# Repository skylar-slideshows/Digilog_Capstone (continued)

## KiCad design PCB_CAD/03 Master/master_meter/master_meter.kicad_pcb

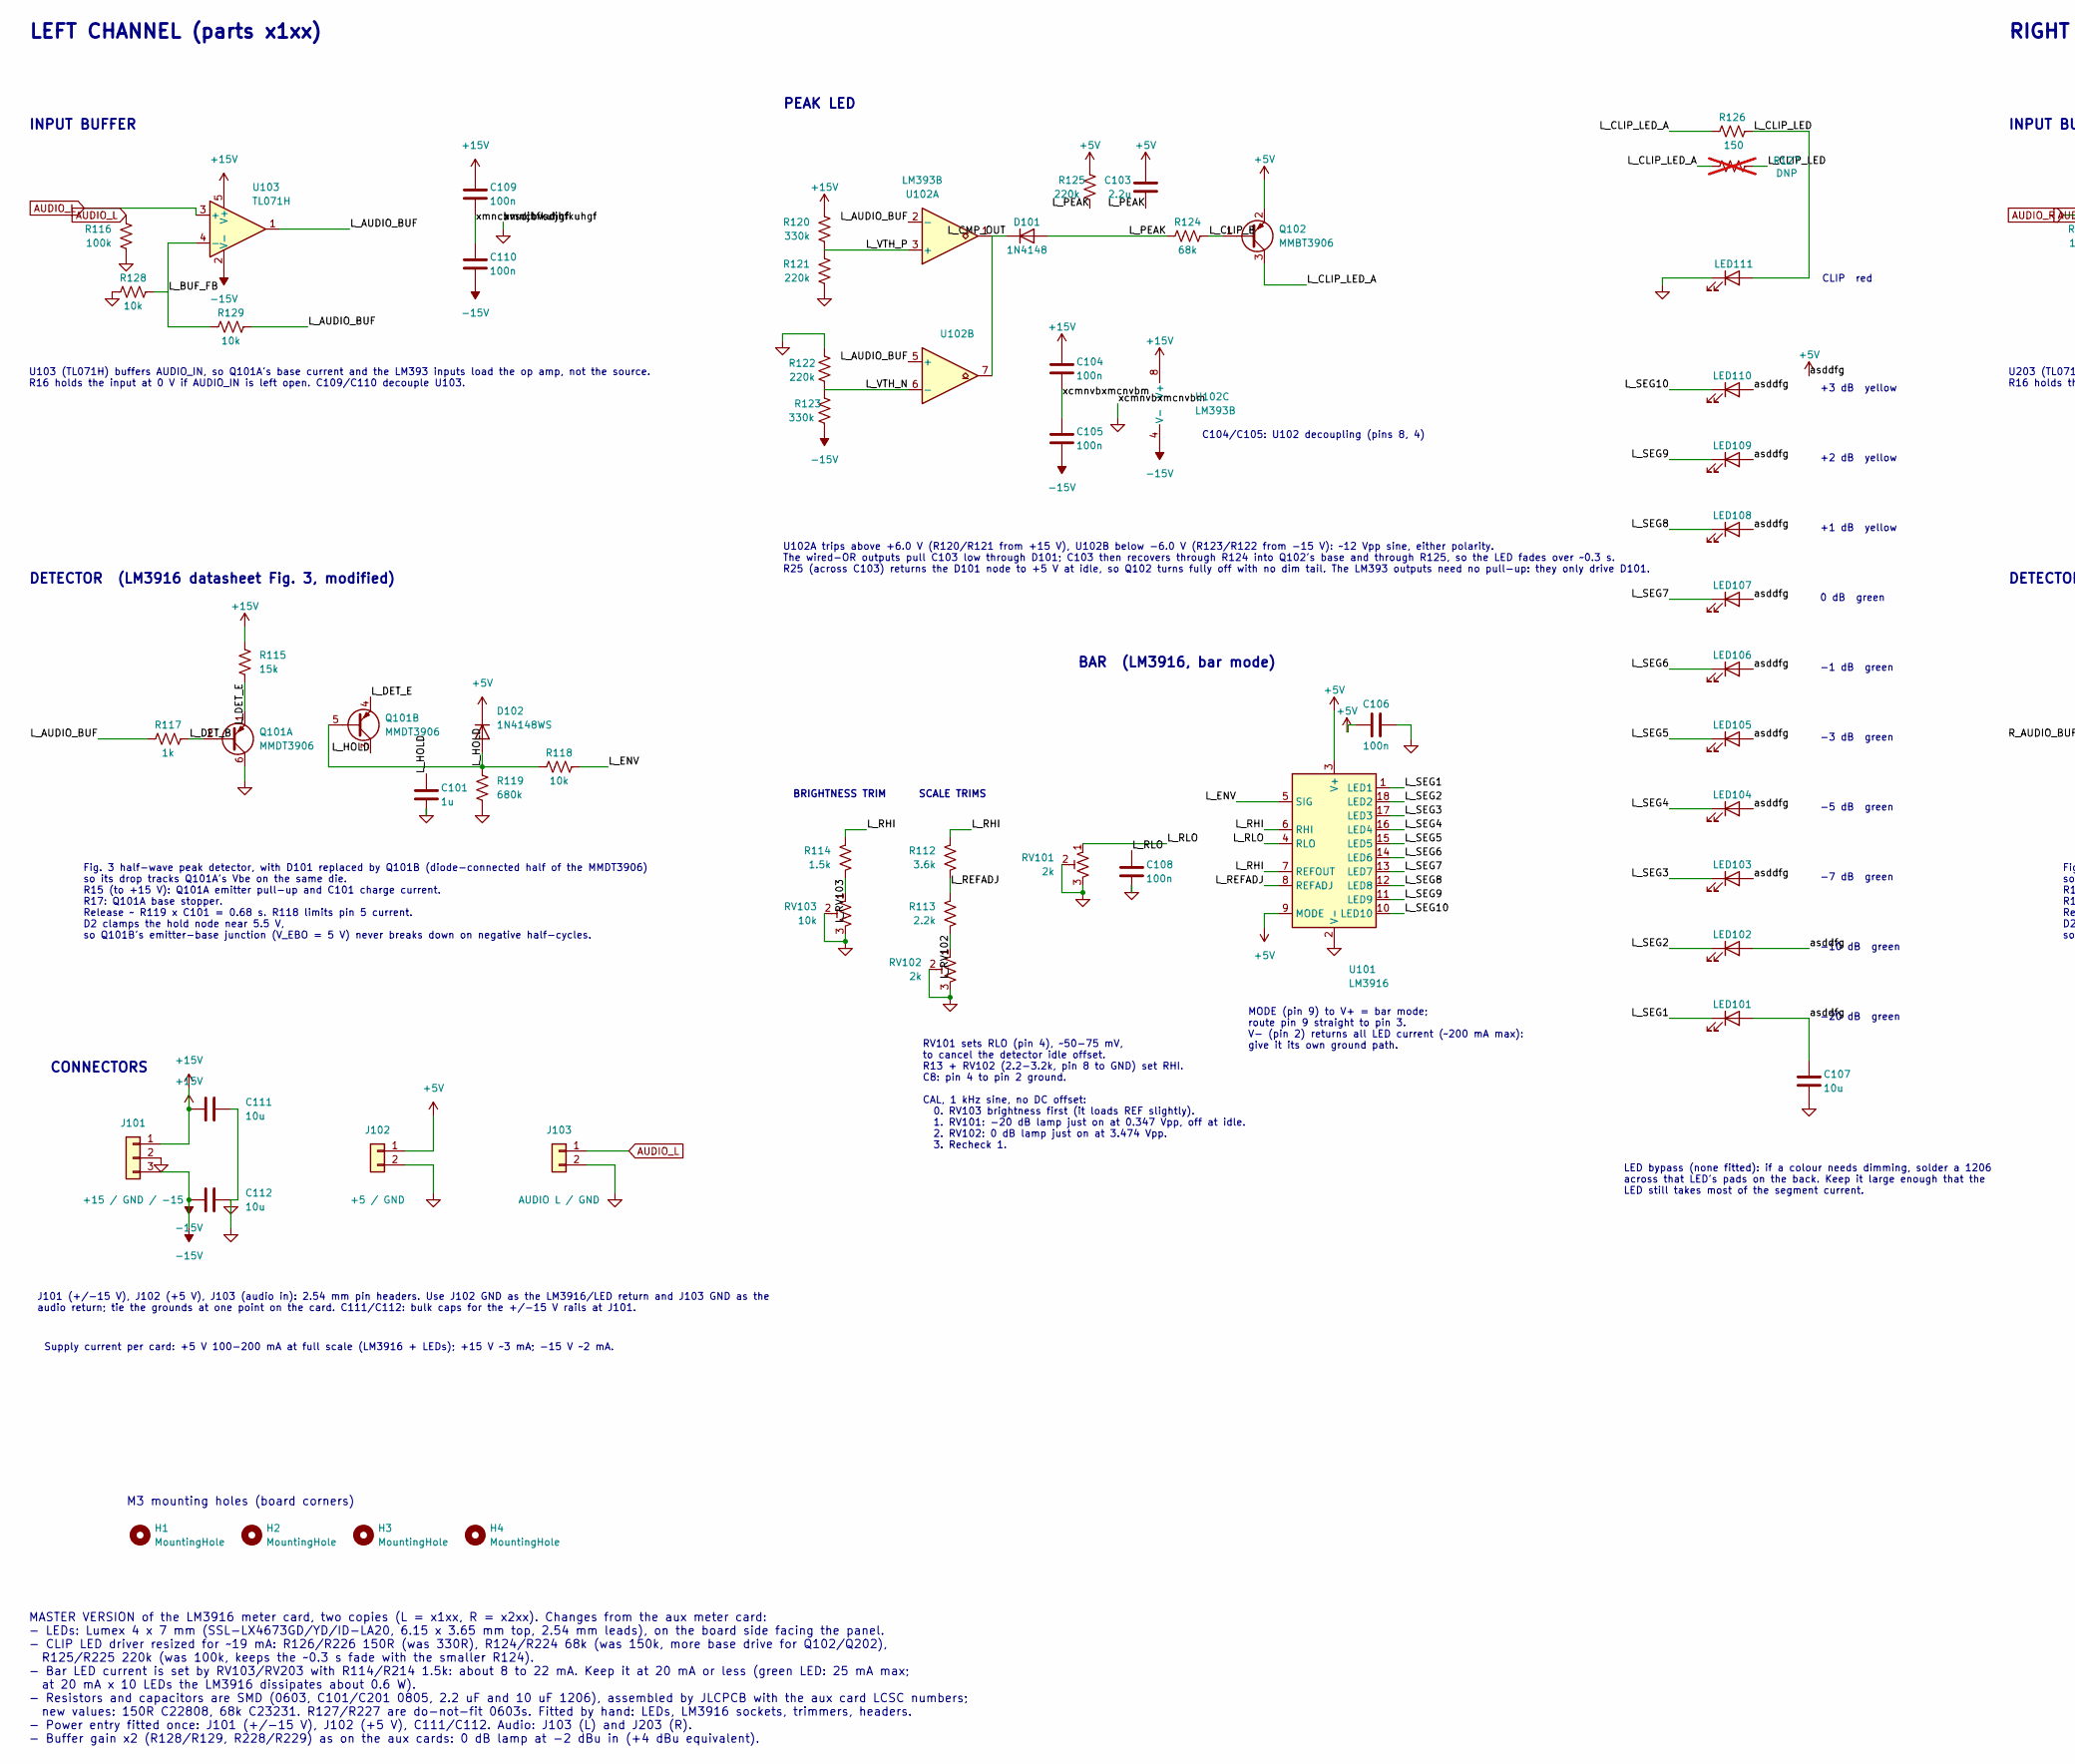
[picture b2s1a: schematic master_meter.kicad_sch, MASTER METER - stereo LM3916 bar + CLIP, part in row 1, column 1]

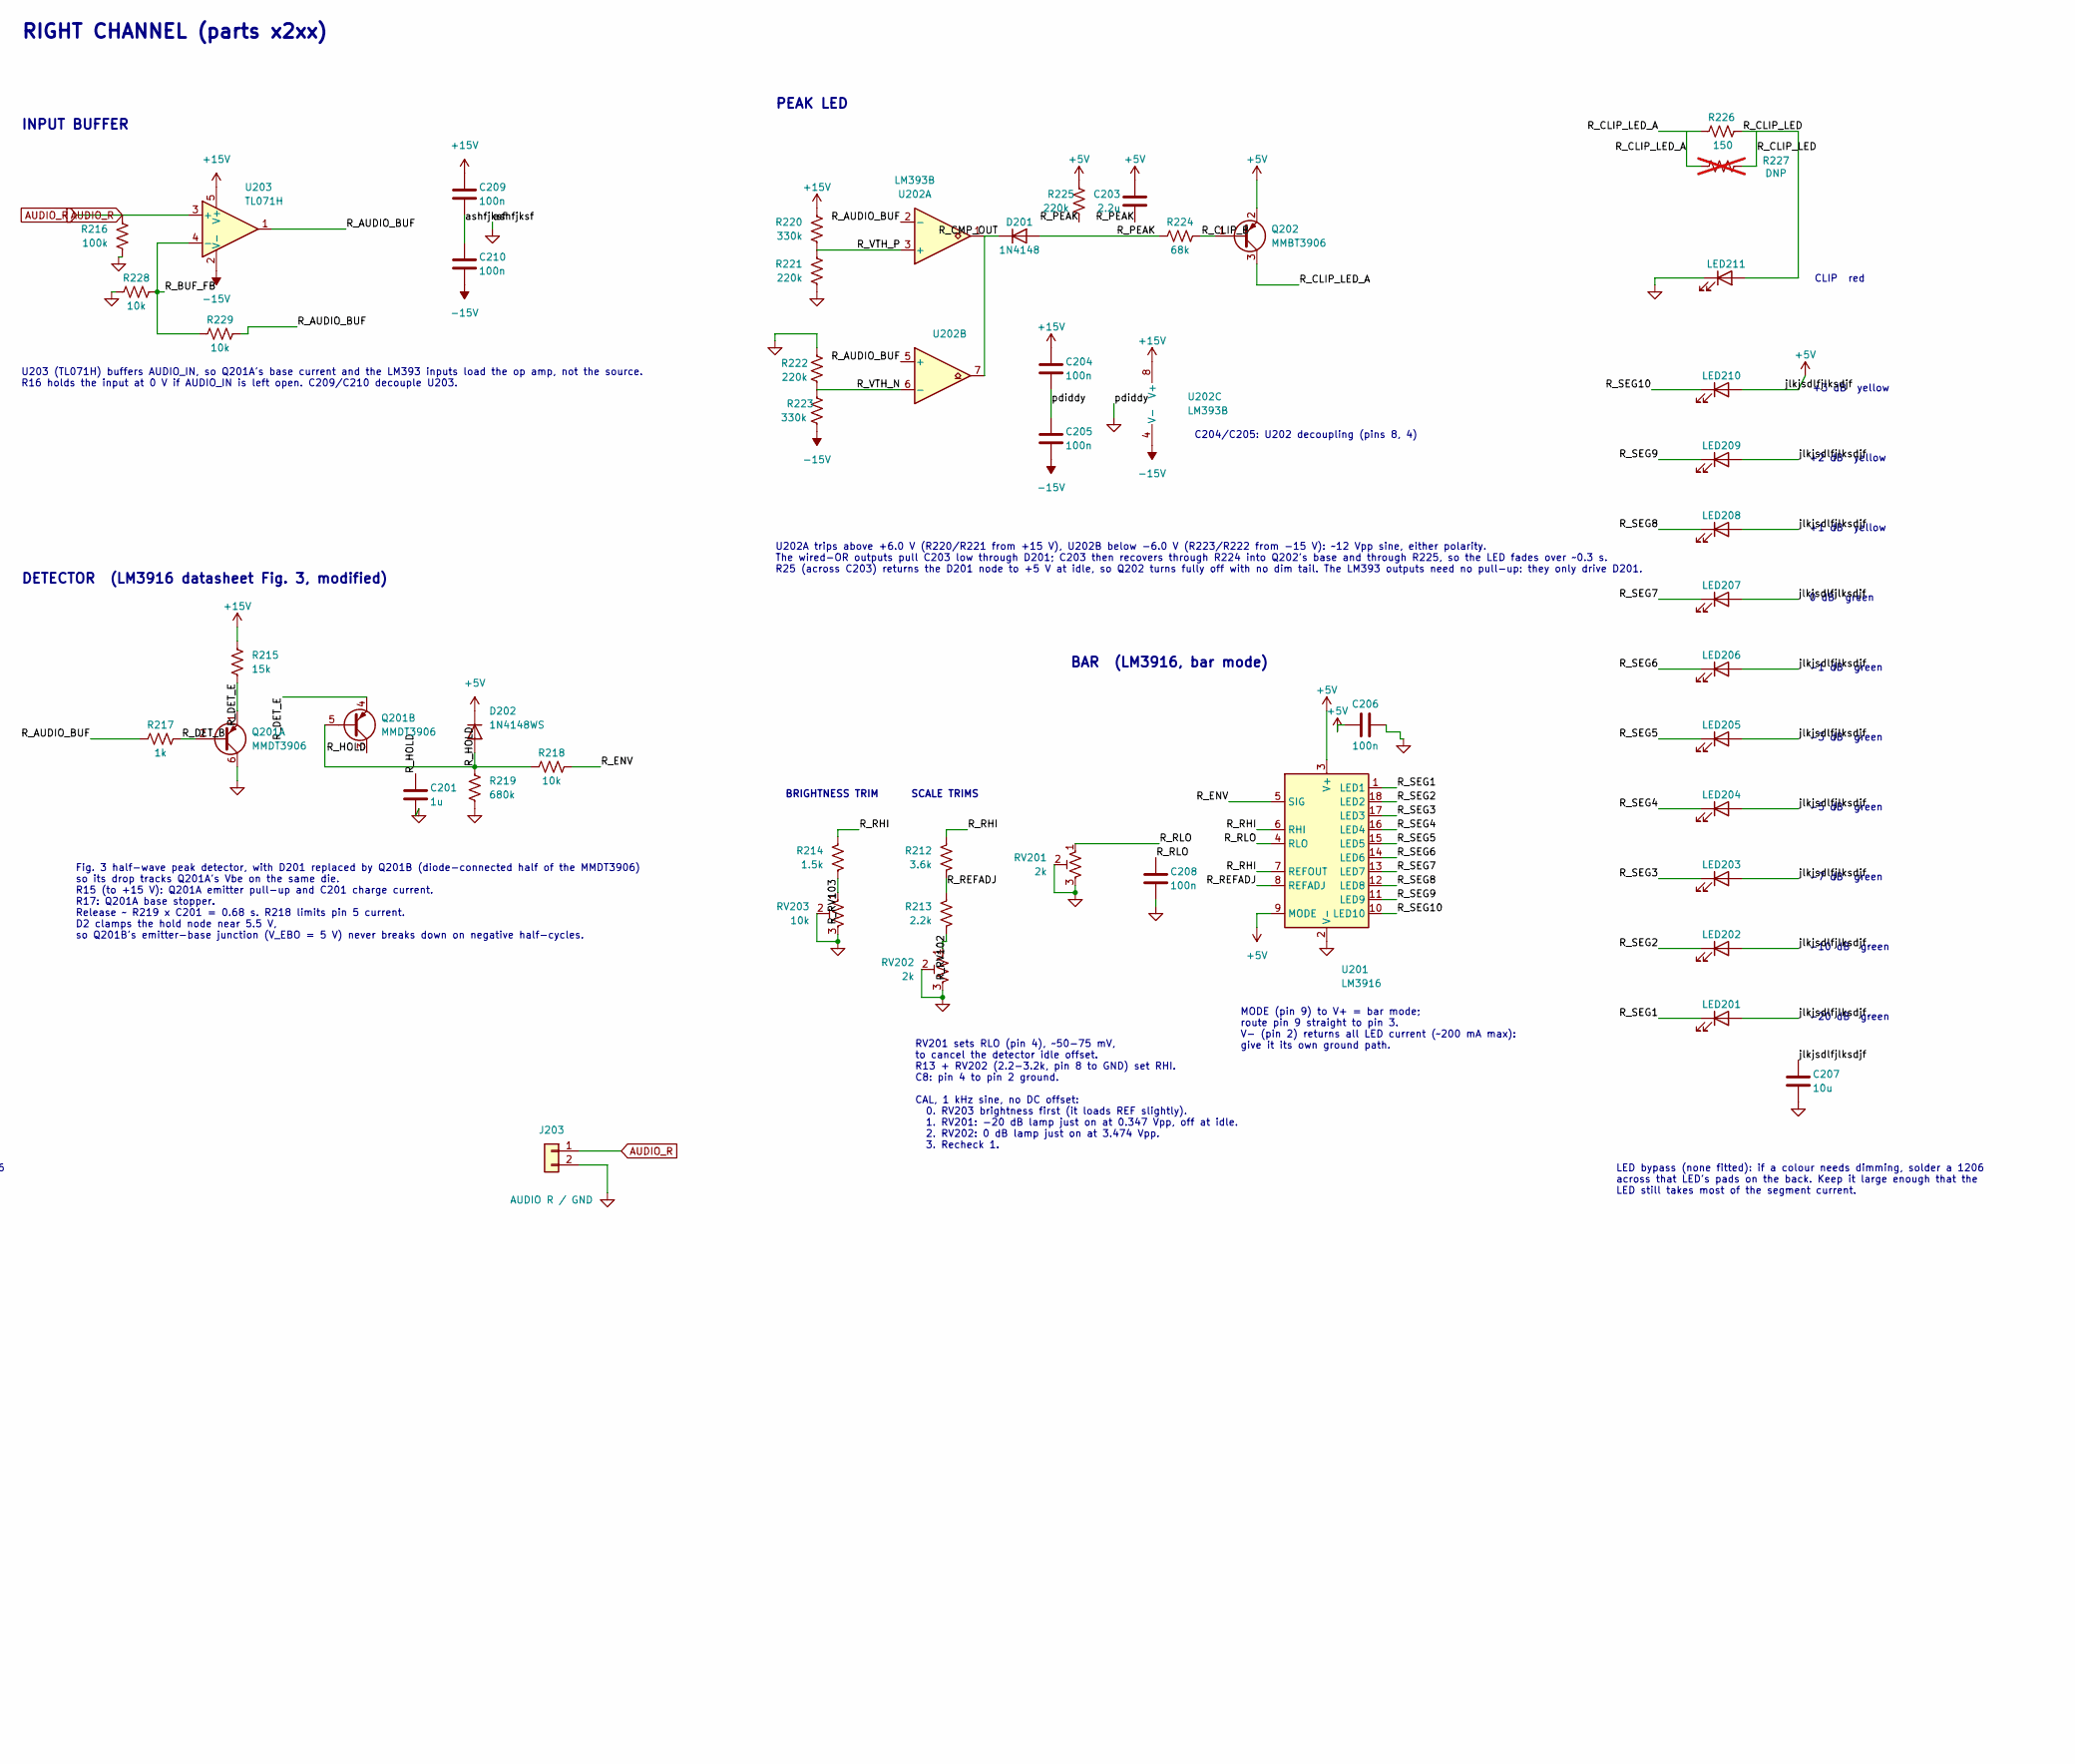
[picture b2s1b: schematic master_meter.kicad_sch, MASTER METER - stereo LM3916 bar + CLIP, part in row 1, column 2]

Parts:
C101, C201: 1u; C_0805_2012Metric; MPN Samsung CL21B105KBFNNNE; LCSC C28323
C103, C203: 2.2u; C_1206_3216Metric; MPN Samsung CL31B225KBHNNNE; LCSC C50254
C104, C105, C106, C108, C109, C110, C204, C205, C206, C208, C209, C210: 100n; C_0603_1608Metric; LCSC C1591
C107, C111, C112, C207: 10u; C_1206_3216Metric; MPN Samsung CL31A106KBHNNNE; LCSC C13585
D101, D201: 1N4148; D_SOD-323; LCSC C2128
D102, D202: 1N4148WS; D_SOD-323; MPN JSCJ 1N4148WS; LCSC C2128
H1, H2, H3, H4: MountingHole; MountingHole_3.2mm_M3
J101: +15 / GND / -15; PinHeader_1x03_P2.54mm_Vertical; LCSC DNP
J102: +5 / GND; PinHeader_1x02_P2.54mm_Vertical; LCSC DNP
J103: AUDIO L / GND; PinHeader_1x02_P2.54mm_Vertical; LCSC DNP
J203: AUDIO R / GND; PinHeader_1x02_P2.54mm_Vertical; LCSC DNP
LED101, LED102, LED103, LED104, LED105, LED106, LED107, LED201, LED202, LED203, LED204, LED205, LED206, LED207: SSL-LX4673GD-LA20 green; LED_Lumex_SSL-LX4673_6.15x3.65mm_P2.54mm; LCSC DNP
LED108, LED109, LED110, LED208, LED209, LED210: SSL-LX4673YD-LA20 yellow; LED_Lumex_SSL-LX4673_6.15x3.65mm_P2.54mm; LCSC DNP
LED111, LED211: SSL-LX4673ID-LA20 red; LED_Lumex_SSL-LX4673_6.15x3.65mm_P2.54mm; LCSC DNP
Q101, Q201: MMDT3906; SOT-363_SC-70-6; LCSC C508227
Q102, Q202: MMBT3906; SOT-23; LCSC C82762
R112, R212: 3.6k; R_0603_1608Metric; MPN UNI-ROYAL 0603WAF3601T5E; LCSC C22980
R113, R213: 2.2k; R_0603_1608Metric; MPN UNI-ROYAL 0603WAF2201T5E; LCSC C4190
R114, R214: 1.5k; R_0603_1608Metric; MPN UNI-ROYAL 0603WAF1501T5E; LCSC C22843
R115, R215: 15k; R_0603_1608Metric; MPN UNI-ROYAL 0603WAF1502T5E; LCSC C22809
R116, R216: 100k; R_0603_1608Metric; MPN UNI-ROYAL 0603WAF1003T5E; LCSC C25803
R117, R217: 1k; R_0603_1608Metric; MPN UNI-ROYAL 0603WAF1001T5E; LCSC C21190
R118, R128, R129, R218, R228, R229: 10k; R_0603_1608Metric; MPN UNI-ROYAL 0603WAF1002T5E; LCSC C25804
R119, R219: 680k; R_0603_1608Metric; MPN UNI-ROYAL 0603WAF6803T5E; LCSC C25822
R120, R123, R220, R223: 330k; R_0603_1608Metric; MPN UNI-ROYAL 0603WAF3303T5E; LCSC C23137
R121, R122, R125, R221, R222, R225: 220k; R_0603_1608Metric; MPN UNI-ROYAL 0603WAF2203T5E; LCSC C22961
R124, R224: 68k; R_0603_1608Metric; MPN UNI-ROYAL 0603WAF6802T5E; LCSC C23231
R126, R226: 150; R_0603_1608Metric; MPN UNI-ROYAL 0603WAF1500T5E; LCSC C22808
R127, R227: DNP; R_0603_1608Metric; LCSC DNP; not fitted
RV101, RV102, RV201, RV202: 2k; Potentiometer_Bourns_3006P_Horizontal; LCSC DNP
RV103, RV203: 10k; Potentiometer_Bourns_3006P_Horizontal; LCSC DNP
U101, U201: LM3916; DIP-18_W7.62mm_Socket; LCSC DNP
U102, U202: LM393B; SOIC-8_3.9x4.9mm_P1.27mm; LCSC C2865059
U103, U203: TL071H; SOT-23-5; MPN TI TL071HIDBVR; LCSC C4370629

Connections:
+5V: C103.1, C106.1, C107.1, C203.1, C206.1, C207.1, D102.1 (K), D202.1 (K), J102.1, LED101.2 (A), LED102.2 (A), LED103.2 (A), LED104.2 (A), LED105.2 (A), LED106.2 (A), LED107.2 (A), LED108.2 (A), LED109.2 (A), LED110.2 (A), LED201.2 (A), LED202.2 (A), LED203.2 (A), LED204.2 (A), LED205.2 (A), LED206.2 (A), LED207.2 (A), LED208.2 (A), LED209.2 (A), LED210.2 (A), Q102.2 (E), Q202.2 (E), R125.1, R225.1, U101.3 (V+), U101.9 (MODE), U201.3 (V+), U201.9 (MODE)
+15V: C104.1, C109.1, C111.1, C204.1, C209.1, J101.1, R115.1, R120.1, R215.1, R220.1, U102.8 (V+), U103.5 (V+), U202.8 (V+), U203.5 (V+)
-15V: C105.2, C110.2, C112.1, C205.2, C210.2, J101.3, R123.2, R223.2, U102.4 (V-), U103.2 (V-), U202.4 (V-), U203.2 (V-)
/L_AUDIO_BUF: R117.1, R129.2, U102.2 (-), U102.5 (+), U103.1
/L_BUF_FB: R128.2, R129.1, U103.4 (-)
/L_CLIP_B: Q102.1 (B), R124.2
/L_CLIP_LED: LED111.2 (A), R126.2, R127.2
/L_CLIP_LED_A: Q102.3 (C), R126.1, R127.1
/L_CMP_OUT: D101.1 (K), U102.1, U102.7
/L_DET_B: Q101.2 (B1), R117.2
/L_DET_E: Q101.1 (E1), Q101.4 (E2), R115.2
/L_ENV: R118.2, U101.5 (SIG)
/L_HOLD: C101.1, D102.2 (A), Q101.3 (C2), Q101.5 (B2), R118.1, R119.1
/L_PEAK: C103.2, D101.2 (A), R124.1, R125.2
/L_REFADJ: R112.2, R113.1, U101.8 (REFADJ)
/L_RHI: R112.1, R114.1, U101.6 (RHI), U101.7 (REFOUT)
/L_RLO: C108.1, RV101.1, U101.4 (RLO)
/L_RV102: R113.2, RV102.1
/L_RV103: R114.2, RV103.1
/L_SEG1: LED101.1 (K), U101.1 (LED1)
/L_SEG2: LED102.1 (K), U101.18 (LED2)
/L_SEG3: LED103.1 (K), U101.17 (LED3)
/L_SEG4: LED104.1 (K), U101.16 (LED4)
/L_SEG5: LED105.1 (K), U101.15 (LED5)
/L_SEG6: LED106.1 (K), U101.14 (LED6)
/L_SEG7: LED107.1 (K), U101.13 (LED7)
/L_SEG8: LED108.1 (K), U101.12 (LED8)
/L_SEG9: LED109.1 (K), U101.11 (LED9)
/L_SEG10: LED110.1 (K), U101.10 (LED10)
/L_VTH_N: R122.2, R123.1, U102.6 (-)
/L_VTH_P: R120.2, R121.1, U102.3 (+)
/R_AUDIO_BUF: R217.1, R229.2, U202.2 (-), U202.5 (+), U203.1
/R_BUF_FB: R228.2, R229.1, U203.4 (-)
/R_CLIP_B: Q202.1 (B), R224.2
/R_CLIP_LED: LED211.2 (A), R226.2, R227.2
/R_CLIP_LED_A: Q202.3 (C), R226.1, R227.1
/R_CMP_OUT: D201.1 (K), U202.1, U202.7
/R_DET_B: Q201.2 (B1), R217.2
/R_DET_E: Q201.1 (E1), Q201.4 (E2), R215.2
/R_ENV: R218.2, U201.5 (SIG)
/R_HOLD: C201.1, D202.2 (A), Q201.3 (C2), Q201.5 (B2), R218.1, R219.1
/R_PEAK: C203.2, D201.2 (A), R224.1, R225.2
/R_REFADJ: R212.2, R213.1, U201.8 (REFADJ)
/R_RHI: R212.1, R214.1, U201.6 (RHI), U201.7 (REFOUT)
/R_RLO: C208.1, RV201.1, U201.4 (RLO)
/R_RV102: R213.2, RV202.1
/R_RV103: R214.2, RV203.1
/R_SEG1: LED201.1 (K), U201.1 (LED1)
/R_SEG2: LED202.1 (K), U201.18 (LED2)
/R_SEG3: LED203.1 (K), U201.17 (LED3)
/R_SEG4: LED204.1 (K), U201.16 (LED4)
/R_SEG5: LED205.1 (K), U201.15 (LED5)
/R_SEG6: LED206.1 (K), U201.14 (LED6)
/R_SEG7: LED207.1 (K), U201.13 (LED7)
/R_SEG8: LED208.1 (K), U201.12 (LED8)
/R_SEG9: LED209.1 (K), U201.11 (LED9)
/R_SEG10: LED210.1 (K), U201.10 (LED10)
/R_VTH_N: R222.2, R223.1, U202.6 (-)
/R_VTH_P: R220.2, R221.1, U202.3 (+)
AUDIO_L: J103.1, R116.1, U103.3 (+)
AUDIO_R: J203.1, R216.1, U203.3 (+)
GND: C101.2, C104.2, C105.1, C106.2, C107.2, C108.2, C109.2, C110.1, C111.2, C112.2, C201.2, C204.2, C205.1, C206.2, C207.2, C208.2, C209.2, C210.1, J101.2, J102.2, J103.2, J203.2, LED111.1 (K), LED211.1 (K), Q101.6 (C1), Q201.6 (C1), R116.2, R119.2, R121.2, R122.1, R128.1, R216.2, R219.2, R221.2, R222.1, R228.1, RV101.2, RV101.3, RV102.2, RV102.3, RV103.2, RV103.3, RV201.2, RV201.3, RV202.2, RV202.3, RV203.2, RV203.3, U101.2 (V-), U201.2 (V-)

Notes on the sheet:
CLIP red
-20 dB green
U103 (TL071H) buffers AUDIO_IN, so Q101A's base current and the LM393 inputs load the op amp, not the source. R16 holds the input at 0 V if AUDIO_IN is left open. C109/C110 decouple U103.
LED bypass (none fitted): if a colour needs dimming, solder a 1206 across that LED's pads on the back. Keep it large enough that the LED still takes most of the segment current.
-3 dB green
DETECTOR (LM3916 datasheet Fig. 3, modified)
U202A trips above +6.0 V (R220/R221 from +15 V), U202B below -6.0 V (R223/R222 from -15 V): ~12 Vpp sine, either polarity. The wired-OR outputs pull C203 low through D201; C203 then recovers through R224 into Q202's base and through R225, so the LED fades over ~0.3 s. R25 (across C203) returns the 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
+1 dB yellow
+3 dB yellow
M3 mounting holes (board corners)
-10 dB green
U203 (TL071H) buffers AUDIO_IN, so Q201A's base current and the LM393 inputs load the op amp, not the source. R16 holds the input at 0 V if AUDIO_IN is left open. C209/C210 decouple U203.
BAR (LM3916, bar mode)
-5 dB green
C104/C105: U102 decoupling (pins 8, 4)
-1 dB green
+2 dB yellow
MODE (pin 9) to V+ = bar mode; route pin 9 straight to pin 3. V- (pin 2) returns all LED current (~200 mA max): give it its own ground path.
CONNECTORS
-7 dB green
INPUT BUFFER
PEAK LED
0 dB green
U102A trips above +6.0 V (R120/R121 from +15 V), U102B below -6.0 V (R123/R122 from -15 V): ~12 Vpp sine, either polarity. The wired-OR outputs pull C103 low through D101; C103 then recovers through R124 into Q102's base and through R125, so the LED fades over ~0.3 s. R25 (across C103) returns the 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
BRIGHTNESS TRIM
RIGHT CHANNEL (parts x2xx)
MASTER VERSION of the LM3916 meter card, two copies (L = x1xx, R = x2xx). Changes from the aux meter card: - LEDs: Lumex 4 x 7 mm (SSL-LX4673GD/YD/ID-LA20, 6.15 x 3.65 mm top, 2.54 mm leads), on the board side facing the panel. - CLIP LED driver resized for ~19 mA: R126/R226 150R (was 330R), R124/R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
Fig. 3 half-wave peak detector, with D201 replaced by Q201B (diode-connected half of the MMDT3906) so its drop tracks Q201A's Vbe on the same die. R15 (to +15 V): Q201A emitter pull-up and C201 charge current. R17: Q201A base stopper. Release ~ R219 x C201 = 0.68 s. R218 limits pin 5 current. D2 cl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
Supply current per card: +5 V 100-200 mA at full scale (LM3916 + LEDs); +15 V ~3 mA; -15 V ~2 mA.
RV101 sets RLO (pin 4), ~50-75 mV, to cancel the detector idle offset. R13 + RV102 (2.2-3.2k, pin 8 to GND) set RHI. C8: pin 4 to pin 2 ground. CAL, 1 kHz sine, no DC offset: 0. RV103 brightness first (it loads REF slightly). 1. RV101: -20 dB lamp just on at 0.347 Vpp, off at idle. 2. RV102: 0 dB l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
SCALE TRIMS
LEFT CHANNEL (parts x1xx)
RV201 sets RLO (pin 4), ~50-75 mV, to cancel the detector idle offset. R13 + RV202 (2.2-3.2k, pin 8 to GND) set RHI. C8: pin 4 to pin 2 ground. CAL, 1 kHz sine, no DC offset: 0. RV203 brightness first (it loads REF slightly). 1. RV201: -20 dB lamp just on at 0.347 Vpp, off at idle. 2. RV202: 0 dB l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
C204/C205: U202 decoupling (pins 8, 4)
J101 (+/-15 V), J102 (+5 V), J103 (audio in): 2.54 mm pin headers. Use J102 GND as the LM3916/LED return and J103 GND as the audio return; tie the grounds at one point on the card. C111/C112: bulk caps for the +/-15 V rails at J101.
Fig. 3 half-wave peak detector, with D101 replaced by Q101B (diode-connected half of the MMDT3906) so its drop tracks Q101A's Vbe on the same die. R15 (to +15 V): Q101A emitter pull-up and C101 charge current. R17: Q101A base stopper. Release ~ R119 x C101 = 0.68 s. R118 limits pin 5 current. D2 cl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

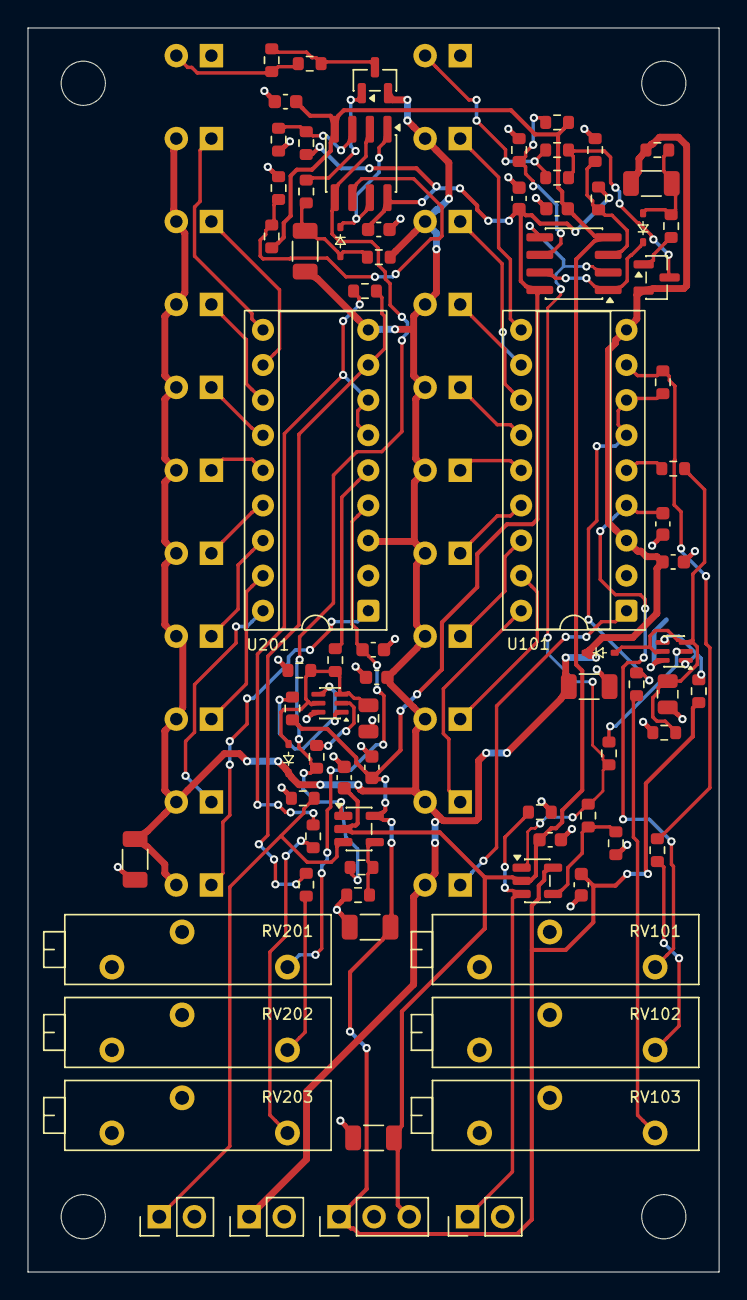
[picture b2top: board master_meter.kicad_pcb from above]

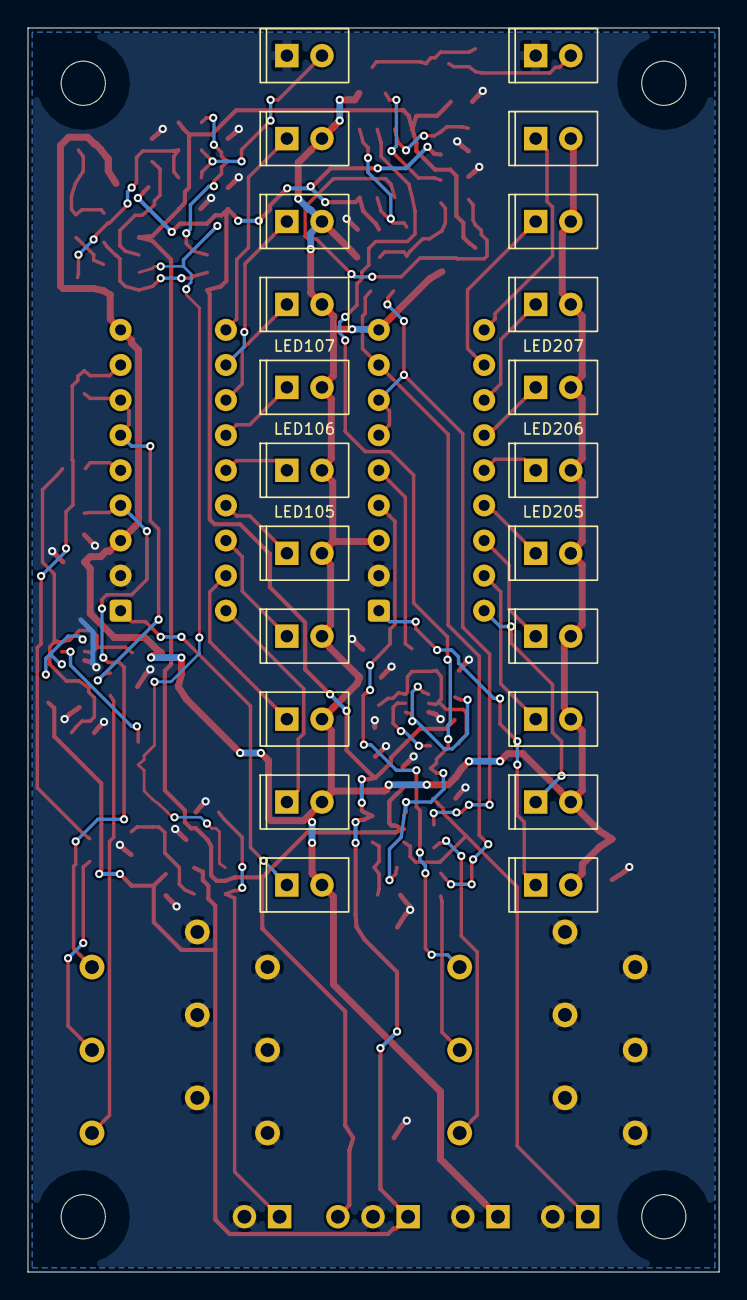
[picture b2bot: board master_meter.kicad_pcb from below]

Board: 2 copper layers, 50.0 x 90.0 mm, 106 parts (22 on the bottom side), 62 nets.

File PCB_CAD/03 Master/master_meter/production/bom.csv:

Designator,Footprint,Quantity,Value,LCSC Part #
"C101, C201",0805,2,1u,C28323
"C103, C203",1206,2,2.2u,C50254
"C104, C105, C106, C108, C109, C110, C204, C205, C206, C208, C209, C210",0603,12,100n,C1591
"C107, C111, C112, C207",1206,4,10u,C13585
"D101, D201",D_SOD-323,2,1N4148,C2128
"D102, D202",D_SOD-323,2,1N4148WS,C2128
J101,PinHeader_1x03_P2.54mm_Vertical,1,+15 / GND / -15,DNP
J102,PinHeader_1x02_P2.54mm_Vertical,1,+5 / GND,DNP
J103,PinHeader_1x02_P2.54mm_Vertical,1,AUDIO L / GND,DNP
J203,PinHeader_1x02_P2.54mm_Vertical,1,AUDIO R / GND,DNP
"LED101, LED102, LED103, LED104, LED105, LED106, LED107, LED201, LED202, LED203, LED204, LED205, LED206, LED207",LED_Lumex_SSL-LX4673_6.15x3.65mm_P2.54mm,14,SSL-LX4673GD-LA20 green,DNP
"LED108, LED109, LED110, LED208, LED209, LED210",LED_Lumex_SSL-LX4673_6.15x3.65mm_P2.54mm,6,SSL-LX4673YD-LA20 yellow,DNP
"LED111, LED211",LED_Lumex_SSL-LX4673_6.15x3.65mm_P2.54mm,2,SSL-LX4673ID-LA20 red,DNP
"Q101, Q201",SOT-363_SC-70-6,2,MMDT3906,C508227
"Q102, Q202",SOT-23,2,MMBT3906,C82762
"R112, R212",0603,2,3.6k,C22980
"R113, R213",0603,2,2.2k,C4190
"R114, R214",0603,2,1.5k,C22843
"R115, R215",0603,2,15k,C22809
"R116, R216",0603,2,100k,C25803
"R117, R217",0603,2,1k,C21190
"R118, R128, R129, R218, R228, R229",0603,6,10k,C25804
"R119, R219",0603,2,680k,C25822
"R120, R123, R220, R223",0603,4,330k,C23137
"R121, R122, R125, R221, R222, R225",0603,6,220k,C22961
"R124, R224",0603,2,68k,C23231
"R126, R226",0603,2,150,C22808
"RV101, RV102, RV201, RV202",Potentiometer_Bourns_3006P_Horizontal,4,2k,DNP
"RV103, RV203",Potentiometer_Bourns_3006P_Horizontal,2,10k,DNP
"U101, U201",DIP-18_W7.62mm_Socket,2,LM3916,DNP
"U102, U202",SOIC-8_3.9x4.9mm_P1.27mm,2,LM393B,C2865059
"U103, U203",SOT-23-5,2,TL071H,C4370629

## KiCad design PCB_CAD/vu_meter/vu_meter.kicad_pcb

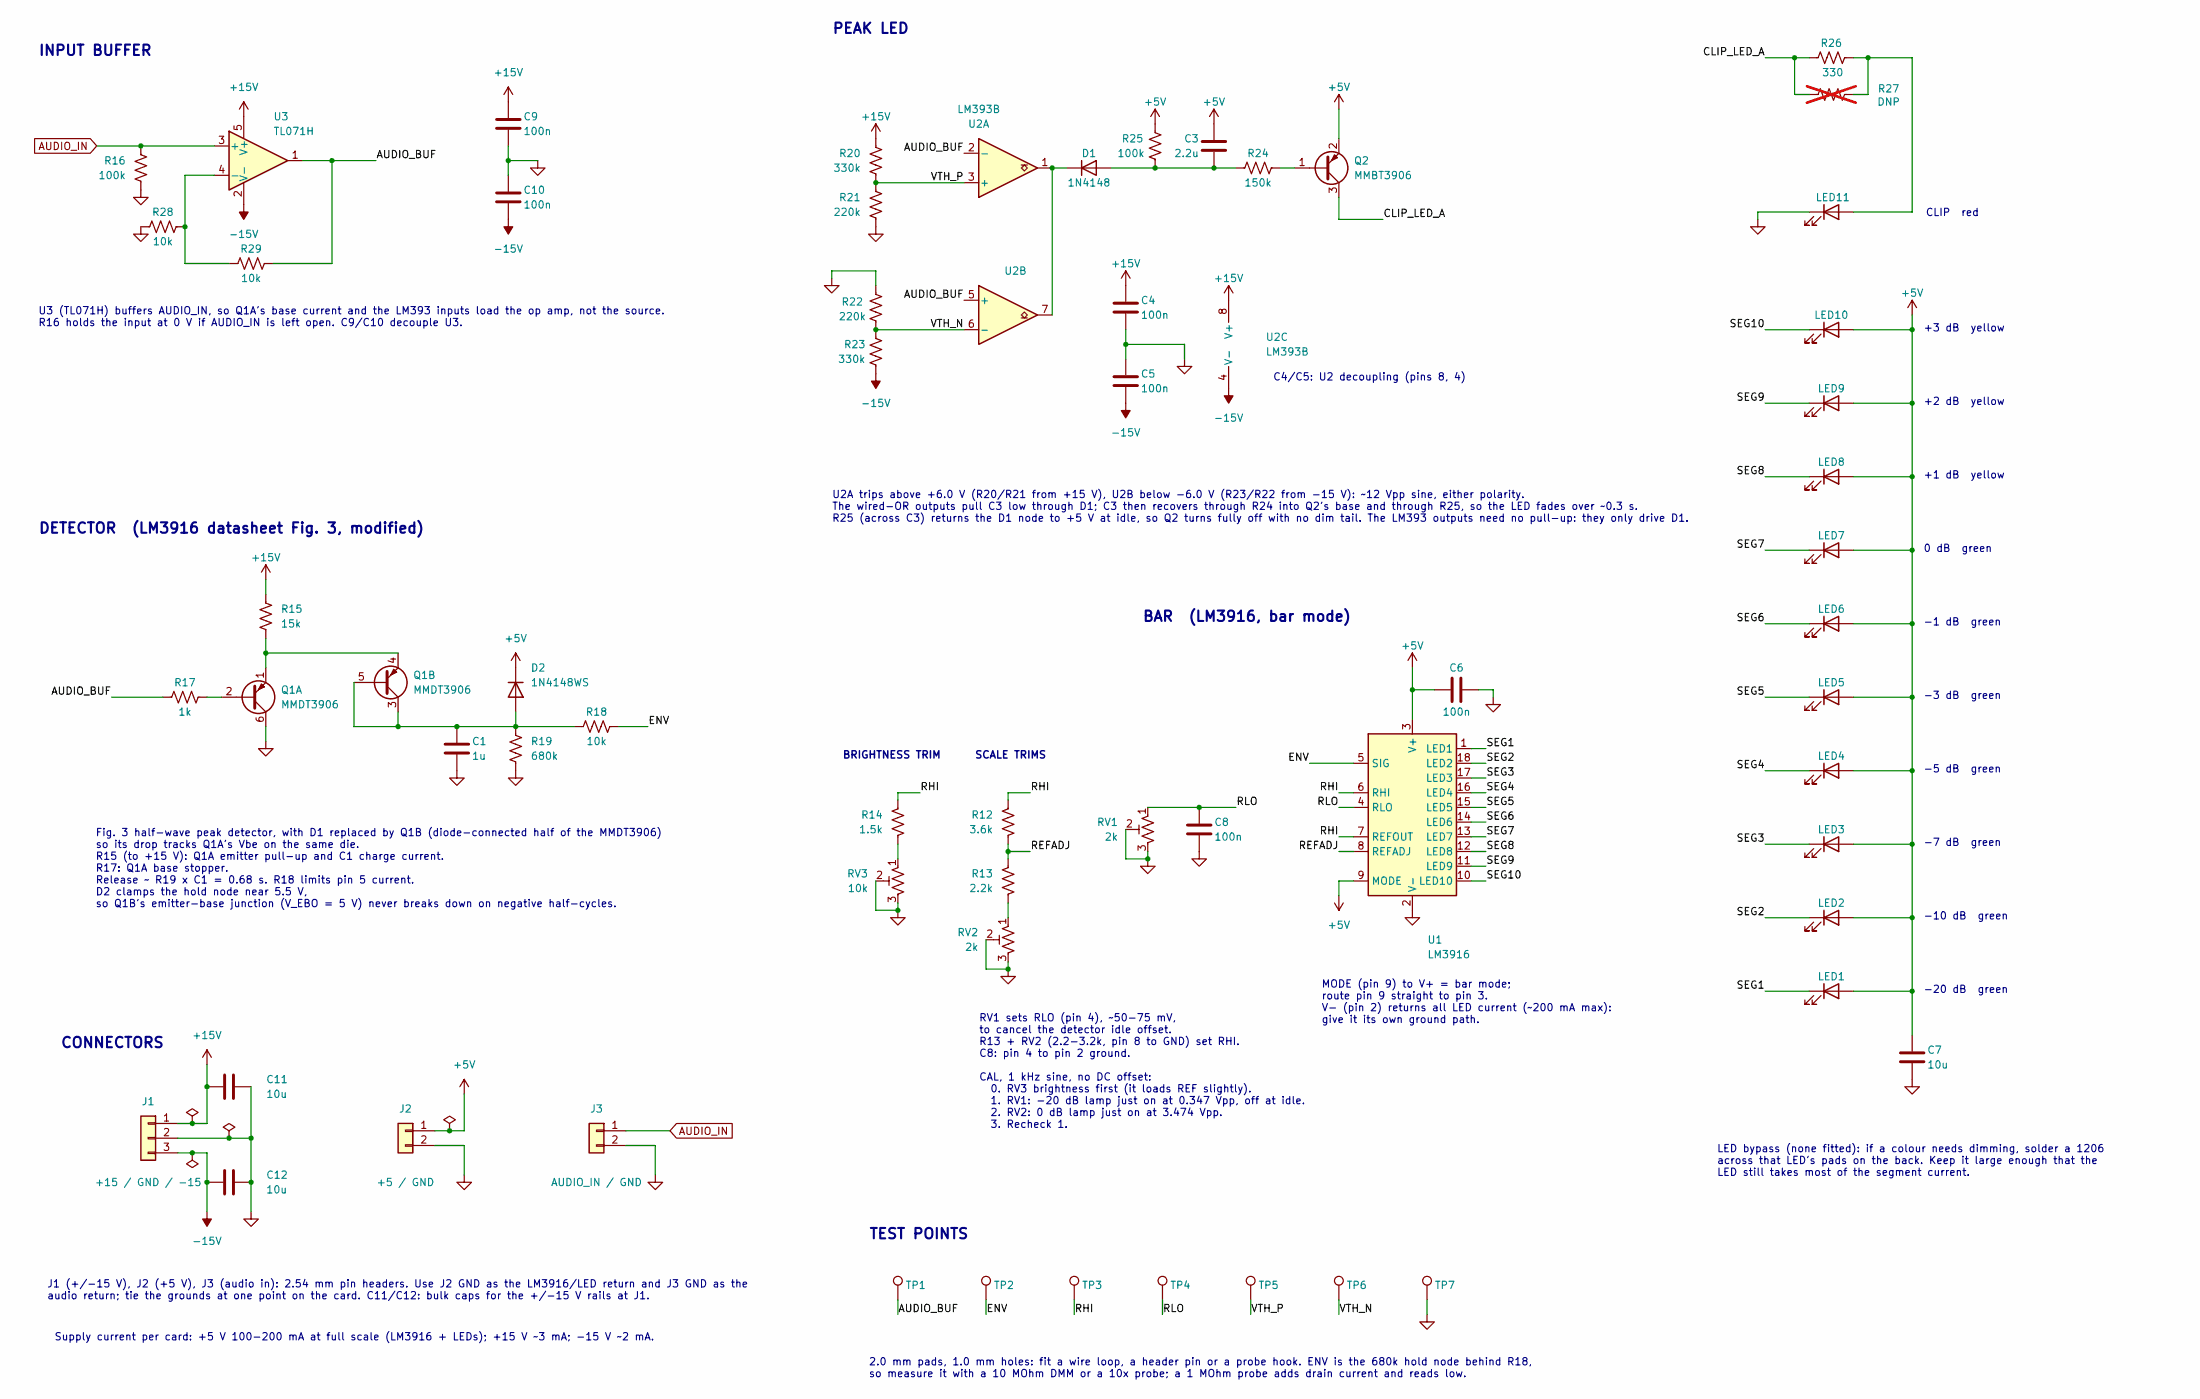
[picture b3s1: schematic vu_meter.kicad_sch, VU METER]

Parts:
C1: 1u; C_0805_2012Metric; MPN Samsung CL21B105KBFNNNE; LCSC C28323
C3: 2.2u; C_1206_3216Metric; MPN Samsung CL31B225KBHNNNE; LCSC C50254
C4, C5, C6, C8, C9, C10: 100n; C_0603_1608Metric; LCSC C1591
C7, C11, C12: 10u; C_1206_3216Metric; MPN Samsung CL31A106KBHNNNE; LCSC C13585
D1: 1N4148; D_SOD-323; LCSC C2128
D2: 1N4148WS; D_SOD-323; MPN JSCJ 1N4148WS; LCSC C2128
J1: +15 / GND / -15; PinHeader_1x03_P2.54mm_Vertical; LCSC DNP
J2: +5 / GND; PinHeader_1x02_P2.54mm_Vertical; LCSC DNP
J3: AUDIO_IN / GND; PinHeader_1x02_P2.54mm_Vertical; LCSC DNP
LED1, LED2, LED3, LED4, LED5, LED6, LED7: LED green; LED_Rectangular_W5.0mm_H2.0mm; LCSC DNP
LED8, LED9, LED10: LED yellow; LED_Rectangular_W5.0mm_H2.0mm; LCSC DNP
LED11: PEAK red; LED_Rectangular_W5.0mm_H2.0mm; LCSC DNP
Q1: MMDT3906; SOT-363_SC-70-6; LCSC C508227
Q2: MMBT3906; SOT-23; LCSC C82762
R12: 3.6k; R_0603_1608Metric; MPN UNI-ROYAL 0603WAF3601T5E; LCSC C22980
R13: 2.2k; R_0603_1608Metric; MPN UNI-ROYAL 0603WAF2201T5E; LCSC C4190
R14: 1.5k; R_0603_1608Metric; MPN UNI-ROYAL 0603WAF1501T5E; LCSC C22843
R15: 15k; R_0603_1608Metric; MPN UNI-ROYAL 0603WAF1502T5E; LCSC C22809
R16, R25: 100k; R_0603_1608Metric; MPN UNI-ROYAL 0603WAF1003T5E; LCSC C25803
R17: 1k; R_0603_1608Metric; MPN UNI-ROYAL 0603WAF1001T5E; LCSC C21190
R18, R28, R29: 10k; R_0603_1608Metric; MPN UNI-ROYAL 0603WAF1002T5E; LCSC C25804
R19: 680k; R_0603_1608Metric; MPN UNI-ROYAL 0603WAF6803T5E; LCSC C25822
R20, R23: 330k; R_0603_1608Metric; MPN UNI-ROYAL 0603WAF3303T5E; LCSC C23137
R21, R22: 220k; R_0603_1608Metric; MPN UNI-ROYAL 0603WAF2203T5E; LCSC C22961
R24: 150k; R_0603_1608Metric; MPN UNI-ROYAL 0603WAF1503T5E; LCSC C22807
R26: 330; R_0603_1608Metric; MPN UNI-ROYAL 0603WAF3300T5E; LCSC C23138
R27: DNP; R_Axial_DIN0207_L6.3mm_D2.5mm_P7.62mm_Horizontal; LCSC DNP; not fitted
RV1, RV2: 2k; Potentiometer_Bourns_3006P_Horizontal; LCSC DNP
RV3: 10k; Potentiometer_Bourns_3006P_Horizontal; LCSC DNP
TP1: AUDIO_BUF; TestPoint_THTPad_D2.0mm_Drill1.0mm; LCSC DNP
TP2: ENV; TestPoint_THTPad_D2.0mm_Drill1.0mm; LCSC DNP
TP3: RHI; TestPoint_THTPad_D2.0mm_Drill1.0mm; LCSC DNP
TP4: RLO; TestPoint_THTPad_D2.0mm_Drill1.0mm; LCSC DNP
TP5: VTH_P; TestPoint_THTPad_D2.0mm_Drill1.0mm; LCSC DNP
TP6: VTH_N; TestPoint_THTPad_D2.0mm_Drill1.0mm; LCSC DNP
TP7: GND; TestPoint_THTPad_D2.0mm_Drill1.0mm; LCSC DNP
U1: LM3916; DIP-18_W7.62mm_Socket; LCSC DNP
U2: LM393B; SOIC-8_3.9x4.9mm_P1.27mm; LCSC C2865059
U3: TL071H; SOT-23-5; MPN TI TL071HIDBVR; LCSC C4370629

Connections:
+5V: C3.1, C6.1, C7.1, D2.1 (K), J2.1, LED1.2 (A), LED2.2 (A), LED3.2 (A), LED4.2 (A), LED5.2 (A), LED6.2 (A), LED7.2 (A), LED8.2 (A), LED9.2 (A), LED10.2 (A), Q2.2 (E), R25.1, U1.3 (V+), U1.9 (MODE)
+15V: C4.1, C9.1, C11.1, J1.1, R15.1, R20.1, U2.8 (V+), U3.5 (V+)
-15V: C5.2, C10.2, C12.1, J1.3, R23.2, U2.4 (V-), U3.2 (V-)
/AUDIO_BUF: R17.1, R29.2, TP1.1 (1_1), U2.2 (-), U2.5 (+), U3.1
/CLIP_LED_A: Q2.3 (C), R26.1, R27.1
/ENV: R18.2, TP2.1 (1_1), U1.5 (SIG)
/REFADJ: R12.2, R13.1, U1.8 (REFADJ)
/RHI: R12.1, R14.1, TP3.1 (1_1), U1.6 (RHI), U1.7 (REFOUT)
/RLO: C8.1, RV1.1, TP4.1 (1_1), U1.4 (RLO)
/SEG1: LED1.1 (K), U1.1 (LED1)
/SEG2: LED2.1 (K), U1.18 (LED2)
/SEG3: LED3.1 (K), U1.17 (LED3)
/SEG4: LED4.1 (K), U1.16 (LED4)
/SEG5: LED5.1 (K), U1.15 (LED5)
/SEG6: LED6.1 (K), U1.14 (LED6)
/SEG7: LED7.1 (K), U1.13 (LED7)
/SEG8: LED8.1 (K), U1.12 (LED8)
/SEG9: LED9.1 (K), U1.11 (LED9)
/SEG10: LED10.1 (K), U1.10 (LED10)
/VTH_N: R22.2, R23.1, TP6.1 (1_1), U2.6 (-)
/VTH_P: R20.2, R21.1, TP5.1 (1_1), U2.3 (+)
AUDIO_IN: J3.1, R16.1, U3.3 (+)
GND: C1.2, C4.2, C5.1, C6.2, C7.2, C8.2, C9.2, C10.1, C11.2, C12.2, J1.2, J2.2, J3.2, LED11.1 (K), Q1.6 (C1), R16.2, R19.2, R21.2, R22.1, R28.1, RV1.2, RV1.3, RV2.2, RV2.3, RV3.2, RV3.3, TP7.1 (1_1), U1.2 (V-)
unnamed: C3.2, D1.2 (A), R24.1, R25.2
unnamed: D1.1 (K), U2.1, U2.7
unnamed: C1.1, D2.2 (A), Q1.3 (C2), Q1.5 (B2), R18.1, R19.1
unnamed: LED11.2 (A), R26.2, R27.2
unnamed: Q1.2 (B1), R17.2
unnamed: Q1.1 (E1), Q1.4 (E2), R15.2
unnamed: Q2.1 (B), R24.2
unnamed: R13.2, RV2.1
unnamed: R14.2, RV3.1
unnamed: R28.2, R29.1, U3.4 (-)

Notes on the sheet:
SCALE TRIMS
INPUT BUFFER
LED bypass (none fitted): if a colour needs dimming, solder a 1206 across that LED's pads on the back. Keep it large enough that the LED still takes most of the segment current.
J1 (+/-15 V), J2 (+5 V), J3 (audio in): 2.54 mm pin headers. Use J2 GND as the LM3916/LED return and J3 GND as the audio return; tie the grounds at one point on the card. C11/C12: bulk caps for the +/-15 V rails at J1.
Supply current per card: +5 V 100-200 mA at full scale (LM3916 + LEDs); +15 V ~3 mA; -15 V ~2 mA.
Fig. 3 half-wave peak detector, with D1 replaced by Q1B (diode-connected half of the MMDT3906) so its drop tracks Q1A's Vbe on the same die. R15 (to +15 V): Q1A emitter pull-up and C1 charge current. R17: Q1A base stopper. Release ~ R19 x C1 = 0.68 s. R18 limits pin 5 current. D2 clamps the hold no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
MODE (pin 9) to V+ = bar mode; route pin 9 straight to pin 3. V- (pin 2) returns all LED current (~200 mA max): give it its own ground path.
-20 dB green
-10 dB green
-7 dB green
-5 dB green
-3 dB green
-1 dB green
0 dB green
+1 dB yellow
+2 dB yellow
+3 dB yellow
BAR (LM3916, bar mode)
RV1 sets RLO (pin 4), ~50-75 mV, to cancel the detector idle offset. R13 + RV2 (2.2-3.2k, pin 8 to GND) set RHI. C8: pin 4 to pin 2 ground. CAL, 1 kHz sine, no DC offset: 0. RV3 brightness first (it loads REF slightly). 1. RV1: -20 dB lamp just on at 0.347 Vpp, off at idle. 2. RV2: 0 dB lamp just o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
C4/C5: U2 decoupling (pins 8, 4)
DETECTOR (LM3916 datasheet Fig. 3, modified)
PEAK LED
U2A trips above +6.0 V (R20/R21 from +15 V), U2B below -6.0 V (R23/R22 from -15 V): ~12 Vpp sine, either polarity. The wired-OR outputs pull C3 low through D1; C3 then recovers through R24 into Q2's base and through R25, so the LED fades over ~0.3 s. R25 (across C3) returns the D1 node to +5 V at i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
U3 (TL071H) buffers AUDIO_IN, so Q1A's base current and the LM393 inputs load the op amp, not the source. R16 holds the input at 0 V if AUDIO_IN is left open. C9/C10 decouple U3.
CLIP red
TEST POINTS
CONNECTORS
2.0 mm pads, 1.0 mm holes: fit a wire loop, a header pin or a probe hook. ENV is the 680k hold node behind R18, so measure it with a 10 MOhm DMM or a 10x probe; a 1 MOhm probe adds drain current and reads low.
BRIGHTNESS TRIM
